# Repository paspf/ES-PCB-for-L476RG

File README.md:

# ES-PCB for Nucleo L476RG
The boad was developed for teaching purposes in the embedded systems laboratory. It is connected to the ST-MORPHO connectors on the Nucleo L476RG. It adds 8 LEDs, two buttons, four WS2812b LEDs and a display to the Nucleo. This git contains all KiCad files of the project. In the release section you can find the corresponding gerber files. 

An application demo can be found at [ES-PCB-for-L476RG-demo](https://github.com/paspf/ES-PCB-for-L476RG-demo).

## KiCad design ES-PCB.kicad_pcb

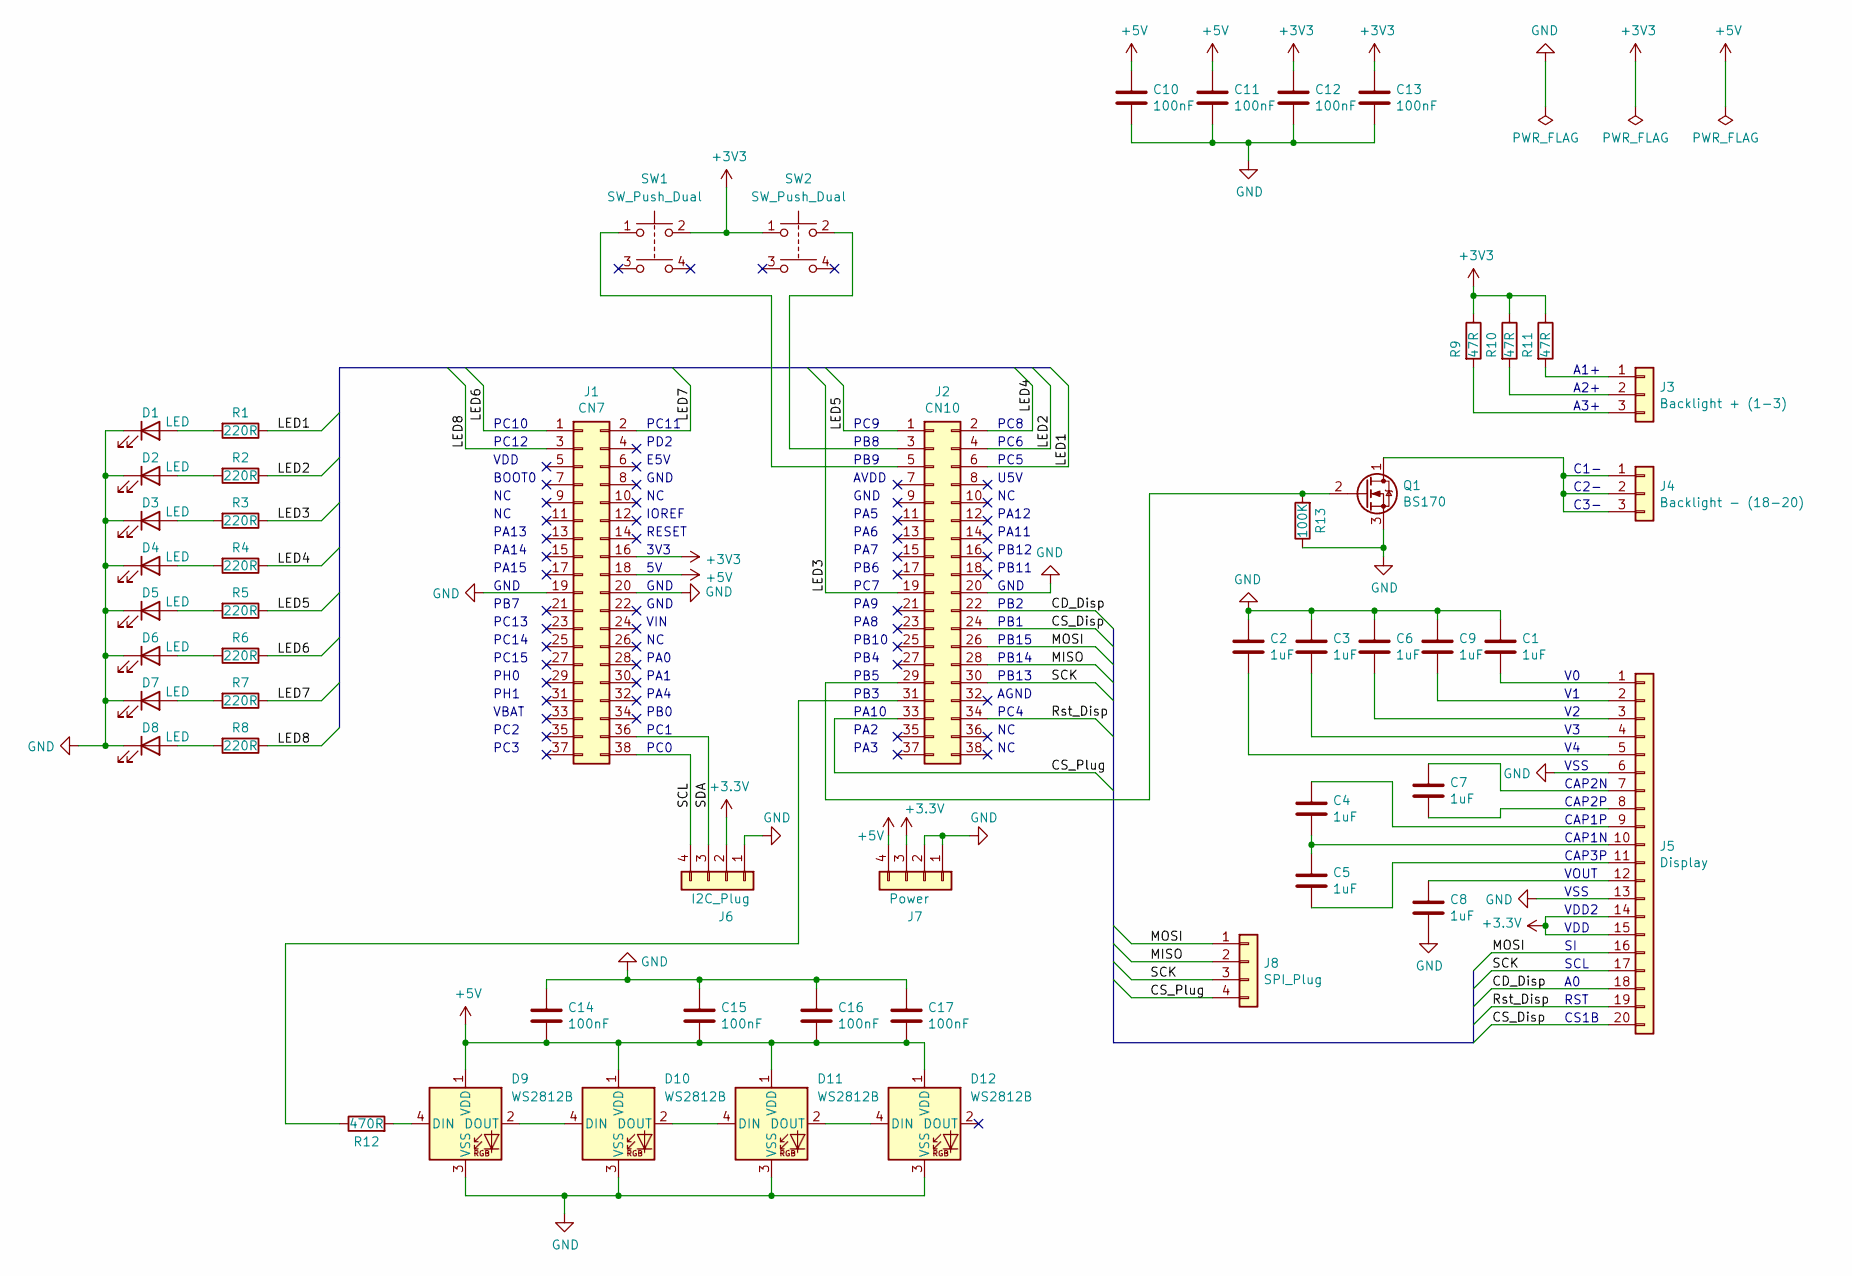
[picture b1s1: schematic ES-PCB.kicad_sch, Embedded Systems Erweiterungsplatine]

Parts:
C1, C2, C3, C4, C5, C6, C7, C8, C9: 1uF; C_Rect_L7.0mm_W2.0mm_P5.00mm
C10, C11, C12, C13, C14, C15, C16, C17: 100nF; C_Disc_D3.0mm_W2.0mm_P2.50mm
D1, D2, D3, D4, D5, D6, D7, D8: LED; LED_D3.0mm_Clear
D9, D10, D11, D12: WS2812B; LED_WS2812B_PLCC4_5.0x5.0mm_P3.2mm
J1: CN7; PinSocket_2x19_P2.54mm_Vertical
J2: CN10; PinSocket_2x19_P2.54mm_Vertical
J3: Backlight + (1-3); PinSocket_1x03_P2.54mm_Vertical
J4: Backlight - (18-20); PinSocket_1x03_P2.54mm_Vertical
J5: Display; PinSocket_1x20_P2.54mm_Vertical
J6: I2C_Plug; PinSocket_1x04_P2.54mm_Vertical
J7: Power; PinSocket_1x04_P2.54mm_Vertical
J8: SPI_Plug; PinSocket_1x04_P2.54mm_Vertical
Q1: BS170; TO-92_Inline
R1, R2, R3, R4, R5, R6, R7, R8: 220R; R_Axial_DIN0207_L6.3mm_D2.5mm_P10.16mm_Horizontal
R9, R10, R11: 47R; R_Axial_DIN0207_L6.3mm_D2.5mm_P10.16mm_Horizontal
R12: 470R; R_Axial_DIN0207_L6.3mm_D2.5mm_P10.16mm_Horizontal
R13: 100K; R_Axial_DIN0207_L6.3mm_D2.5mm_P10.16mm_Horizontal
SW1, SW2: SW_Push_Dual; SW_PUSH_6mm_H5mm

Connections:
+5V: C10.1, C11.1, C14.2, C15.2, C16.2, C17.2, D9.1 (VDD), D10.1 (VDD), D11.1 (VDD), D12.1 (VDD), J1.18, J7.4
/CD_Disp: J2.22, J5.18
/CS_Disp: J2.24, J5.20
/CS_Plug: J2.33, J8.4
/LED1: J2.6, R1.1
/LED2: J2.4, R2.1
/LED3: J2.19, R3.1
/LED4: J2.2, R4.1
/LED5: J2.1, R5.1
/LED6: J1.1, R6.1
/LED7: J1.2, R7.1
/LED8: J1.3, R8.1
/MISO: J2.28, J8.2
/MOSI: J2.26, J5.16, J8.1
/Rst_Disp: J2.34, J5.19
/SCK: J2.30, J5.17, J8.3
/SCL: J1.38, J6.4
/SDA: J1.36, J6.3
GND: C1.1, C2.1, C3.1, C6.1, C8.2, C9.1, C10.2, C11.2, C12.2, C13.2, C14.1, C15.1, C16.1, C17.1, D1.1 (K), D2.1 (K), D3.1 (K), D4.1 (K), D5.1 (K), D6.1 (K), D7.1 (K), D8.1 (K), D9.3 (VSS), D10.3 (VSS), D11.3 (VSS), D12.3 (VSS), J1.19, J1.20, J2.20, J5.6, J5.13, J6.1, J7.1, J7.2, Q1.3 (S), R13.1
unnamed: C1.2, J5.1
unnamed: C2.2, J5.5
unnamed: C3.2, J5.4
unnamed: C4.1, J5.9
unnamed: C4.2, C5.1, J5.10
unnamed: C5.2, J5.11
unnamed: C6.2, J5.3
unnamed: C7.1, J5.7
unnamed: C7.2, J5.8
unnamed: C8.1, J5.12
unnamed: C9.2, J5.2
unnamed: D1.2 (A), R1.2
unnamed: D2.2 (A), R2.2
unnamed: D3.2 (A), R3.2
unnamed: D4.2 (A), R4.2
unnamed: D5.2 (A), R5.2
unnamed: D6.2 (A), R6.2
unnamed: D7.2 (A), R7.2
unnamed: D8.2 (A), R8.2
unnamed: D9.4 (DIN), R12.2
unnamed: D10.2 (DOUT), D11.4 (DIN)
unnamed: D9.2 (DOUT), D10.4 (DIN)
unnamed: D11.2 (DOUT), D12.4 (DIN)
unnamed: J2.3, SW2.2
unnamed: J2.5, SW1.1
unnamed: J2.29, Q1.2 (G), R13.2
unnamed: J2.31, R12.1
unnamed: J3.1, R11.2
unnamed: J3.2, R10.2
unnamed: J3.3, R9.2
unnamed: J4.1, J4.2, J4.3, Q1.1 (D)

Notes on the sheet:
PC5
PH0
GND
PC6
BOOT0
PA13
VDD2
AVDD
PC9
PC7
PA10
IOREF
PA0
PB6
PC11
VDD
RESET
PA11
PA9
CS1B
3V3
PC15
PA4
RST
PB15
PB14
PC12
PB3
CAP1P
C2-
PC1
PB13
CAP2P
PB1
PB8
PA12
PA14
CAP2N
C3-
VSS

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
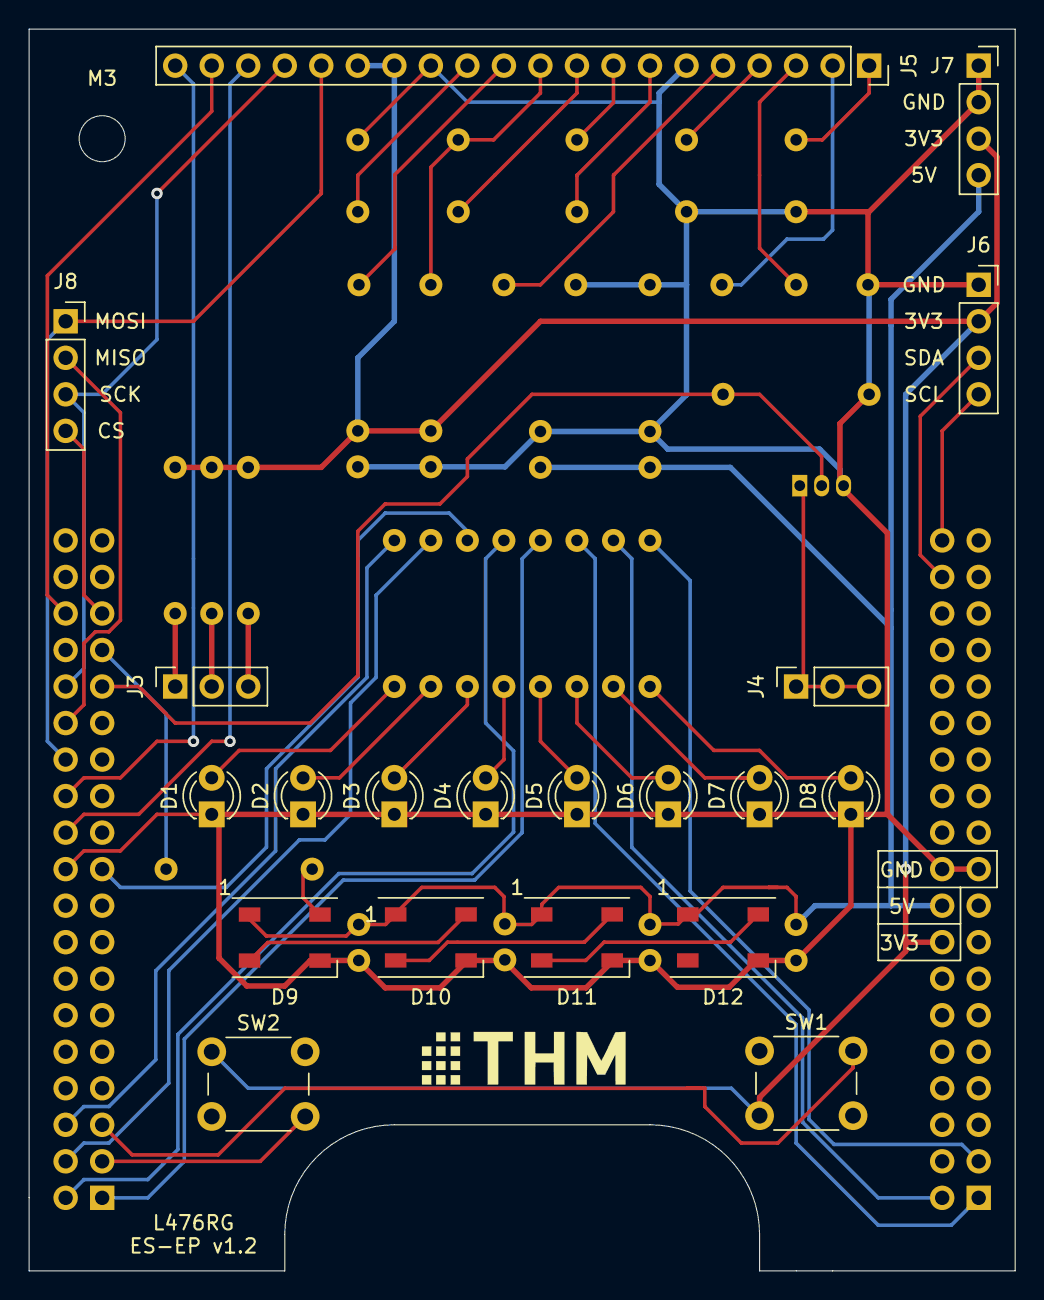
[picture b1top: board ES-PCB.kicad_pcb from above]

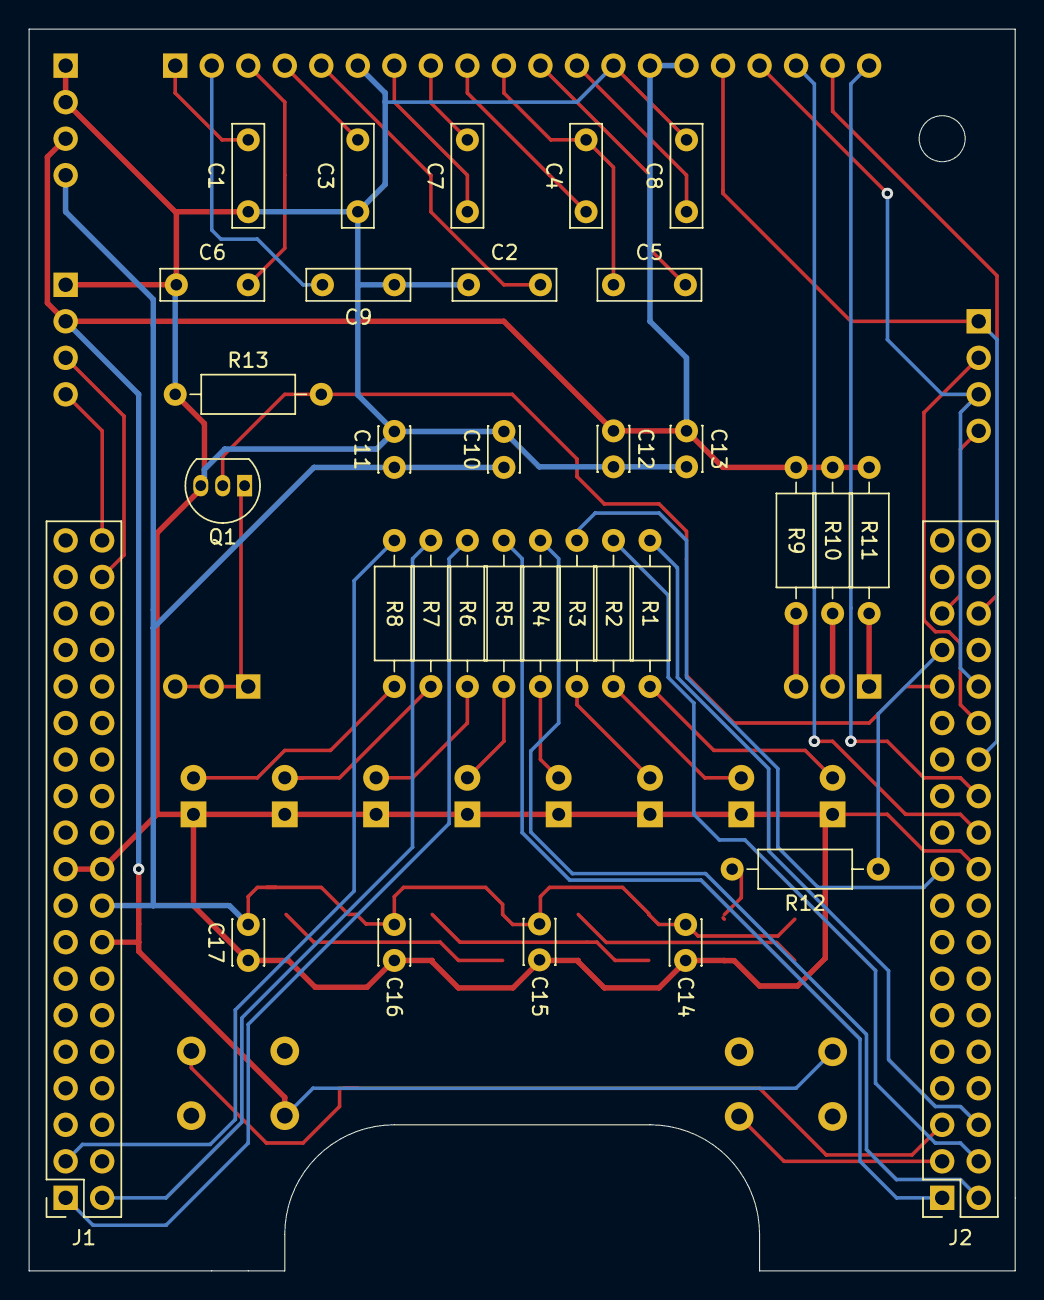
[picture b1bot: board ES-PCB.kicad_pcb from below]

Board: 2 copper layers, 68.6 x 86.4 mm, 54 parts (33 on the bottom side), 51 nets.

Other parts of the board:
M3: MountingHole_3.2mm_M3

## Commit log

2022-05-07 add kiCad project
2022-05-07 Create LICENSE
2024-01-09 Add silkscreen markers for power pins, update to KiCad 7.
